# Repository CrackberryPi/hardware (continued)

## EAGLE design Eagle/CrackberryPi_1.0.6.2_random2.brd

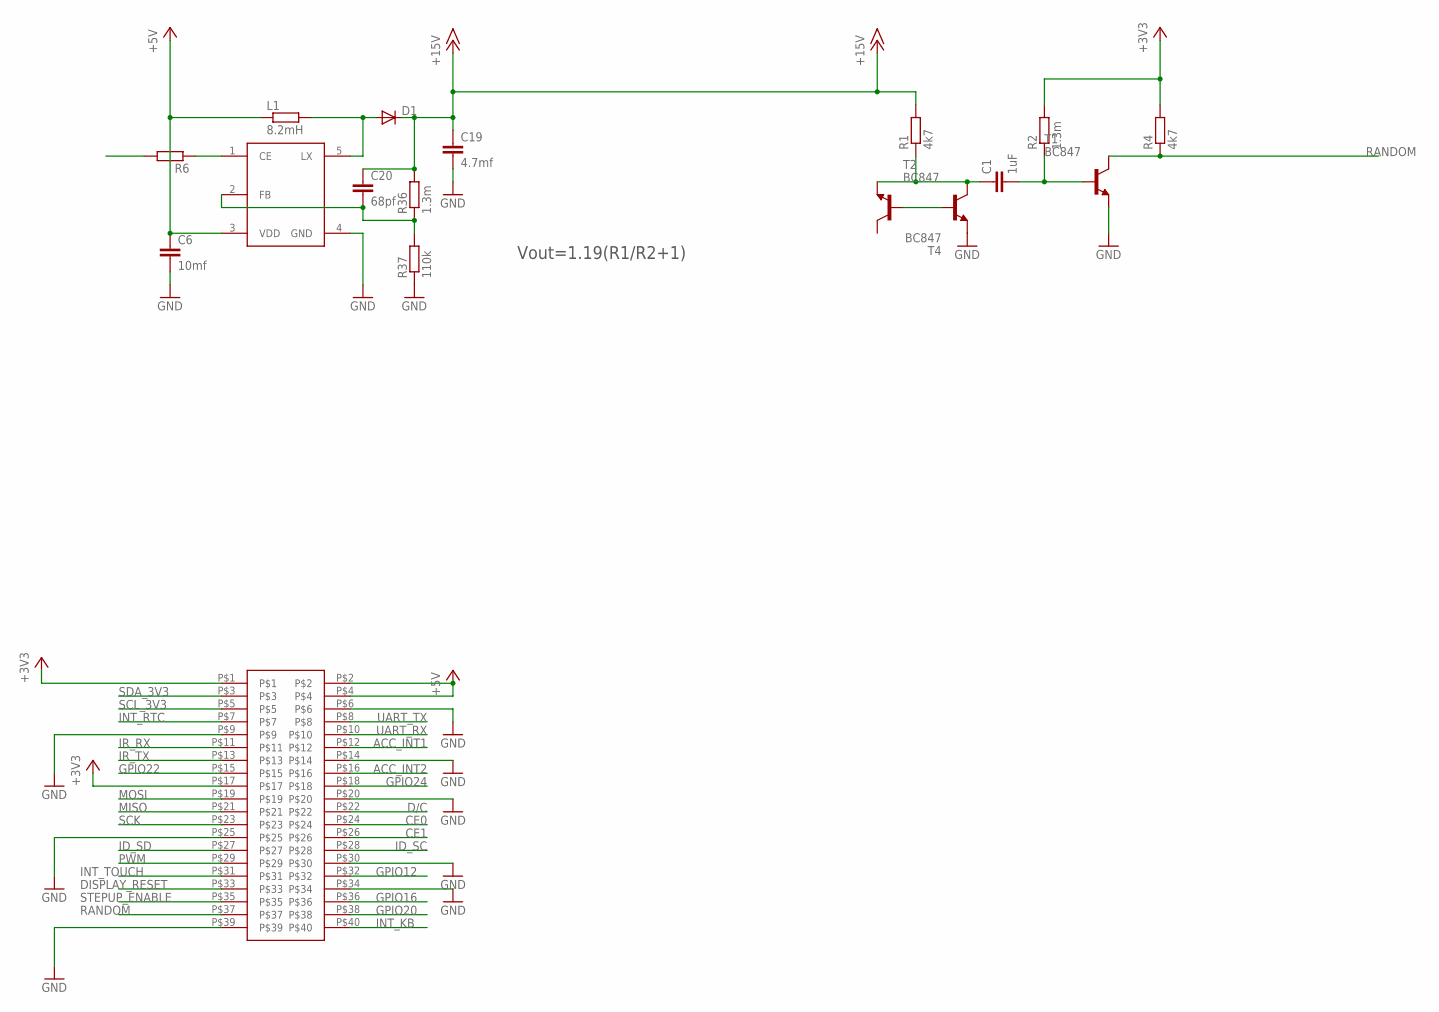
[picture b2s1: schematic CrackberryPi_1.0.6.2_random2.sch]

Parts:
C1: 1uF; C0603
C6: 10mf; C0603
C19: 4.7mf; C0603
C20: 68pf; C0603
D1: DIODE-SOD123; SOD123
L1: 8.2mH; R1210
R1, R4: 4k7; R0603
R2, R36: 1.3m; R0603
R6: R-EU_R1210; R1210
R37: 110k; R0603
T1, T2, T4: BC847; SOT23
U$2: NCP1406; SOT23-5L
U$11: HEADER; 20X2

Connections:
+3V3: R2.2, R4.2, U$11.P$1, U$11.P$17
+5V: C6.1, L1.1, U$2.3 (VDD), U$11.P$2, U$11.P$4
+15V: C19.1, C20.1, D1.C, R1.2, R36.2
ACC_INT1: U$11.P$12
ACC_INT2: U$11.P$16
CE0: U$11.P$24
CE1: U$11.P$26
D/C: U$11.P$22
DISPLAY_RESET: U$11.P$33
FB: C20.2, R36.1, R37.2, U$2.2 (FB)
GND: C6.2, C19.2, R37.1, T1.2 (E), T2.2 (E), U$2.4 (GND), U$11.P$6, U$11.P$9, U$11.P$14, U$11.P$20, U$11.P$25, U$11.P$30, U$11.P$34, U$11.P$39
GPIO12: U$11.P$32
GPIO16: U$11.P$36
GPIO20: U$11.P$38
GPIO22: U$11.P$15
GPIO24: U$11.P$18
ID_SC: U$11.P$28
ID_SD: U$11.P$27
INT_KB: U$11.P$40
INT_RTC: U$11.P$7
INT_TOUCH: U$11.P$31
IR_RX: U$11.P$11
IR_TX: U$11.P$13
LX: D1.A, L1.2, U$2.5 (LX)
MISO: U$11.P$21
MOSI: U$11.P$19
unnamed: R6.1, U$2.1 (CE)
unnamed: T2.1 (B), T4.1 (B)
unnamed: C1.1, R1.1, T2.3 (C), T4.2 (E)
unnamed: C1.2, R2.1, T1.1 (B)
PWM: U$11.P$29
RANDOM: R4.1, T1.3 (C), U$11.P$37
SCK: U$11.P$23
SCL_3V3: U$11.P$5
SDA_3V3: U$11.P$3
STEPUP_ENABLE: R6.2, U$11.P$35
UART_RX: U$11.P$10
UART_TX: U$11.P$8

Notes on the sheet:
Vout=1.19(R1/R2+1)

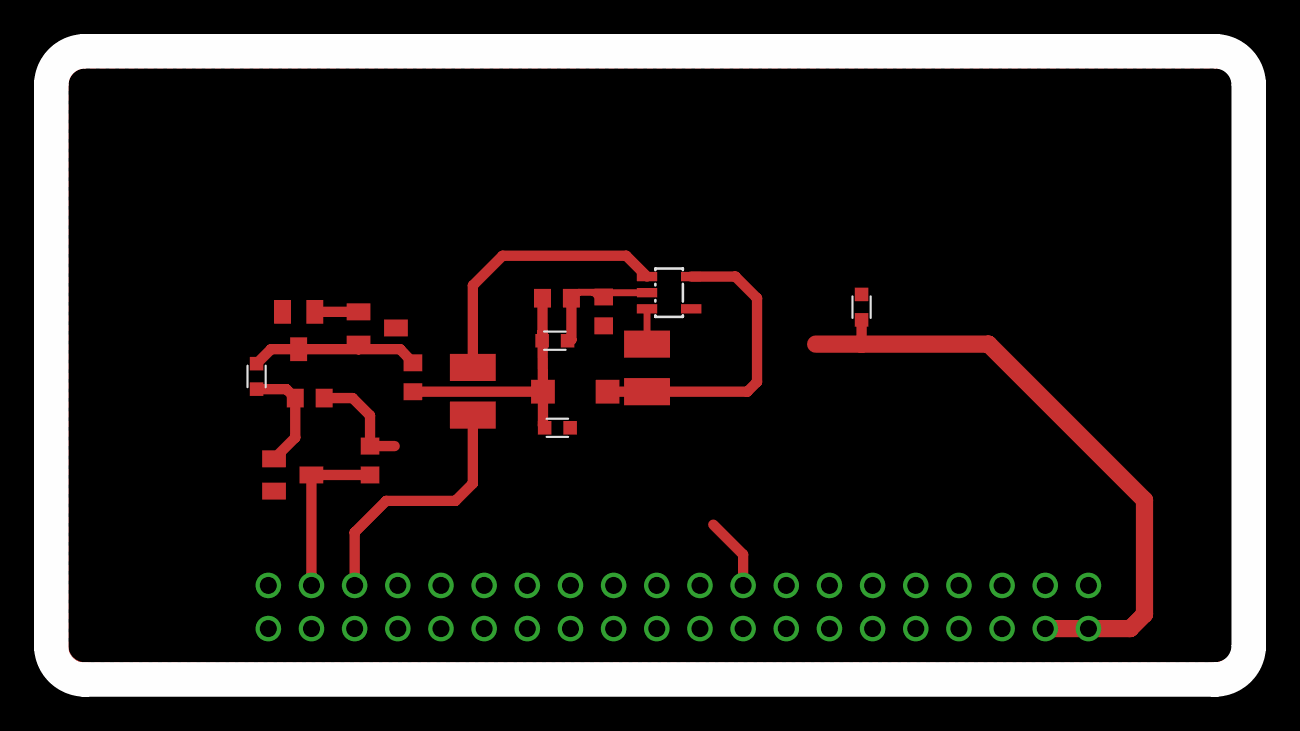
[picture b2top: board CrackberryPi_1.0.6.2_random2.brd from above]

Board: 2 copper layers, 70.5 x 37.0 mm, 17 parts (0 on the bottom side), 12 nets.

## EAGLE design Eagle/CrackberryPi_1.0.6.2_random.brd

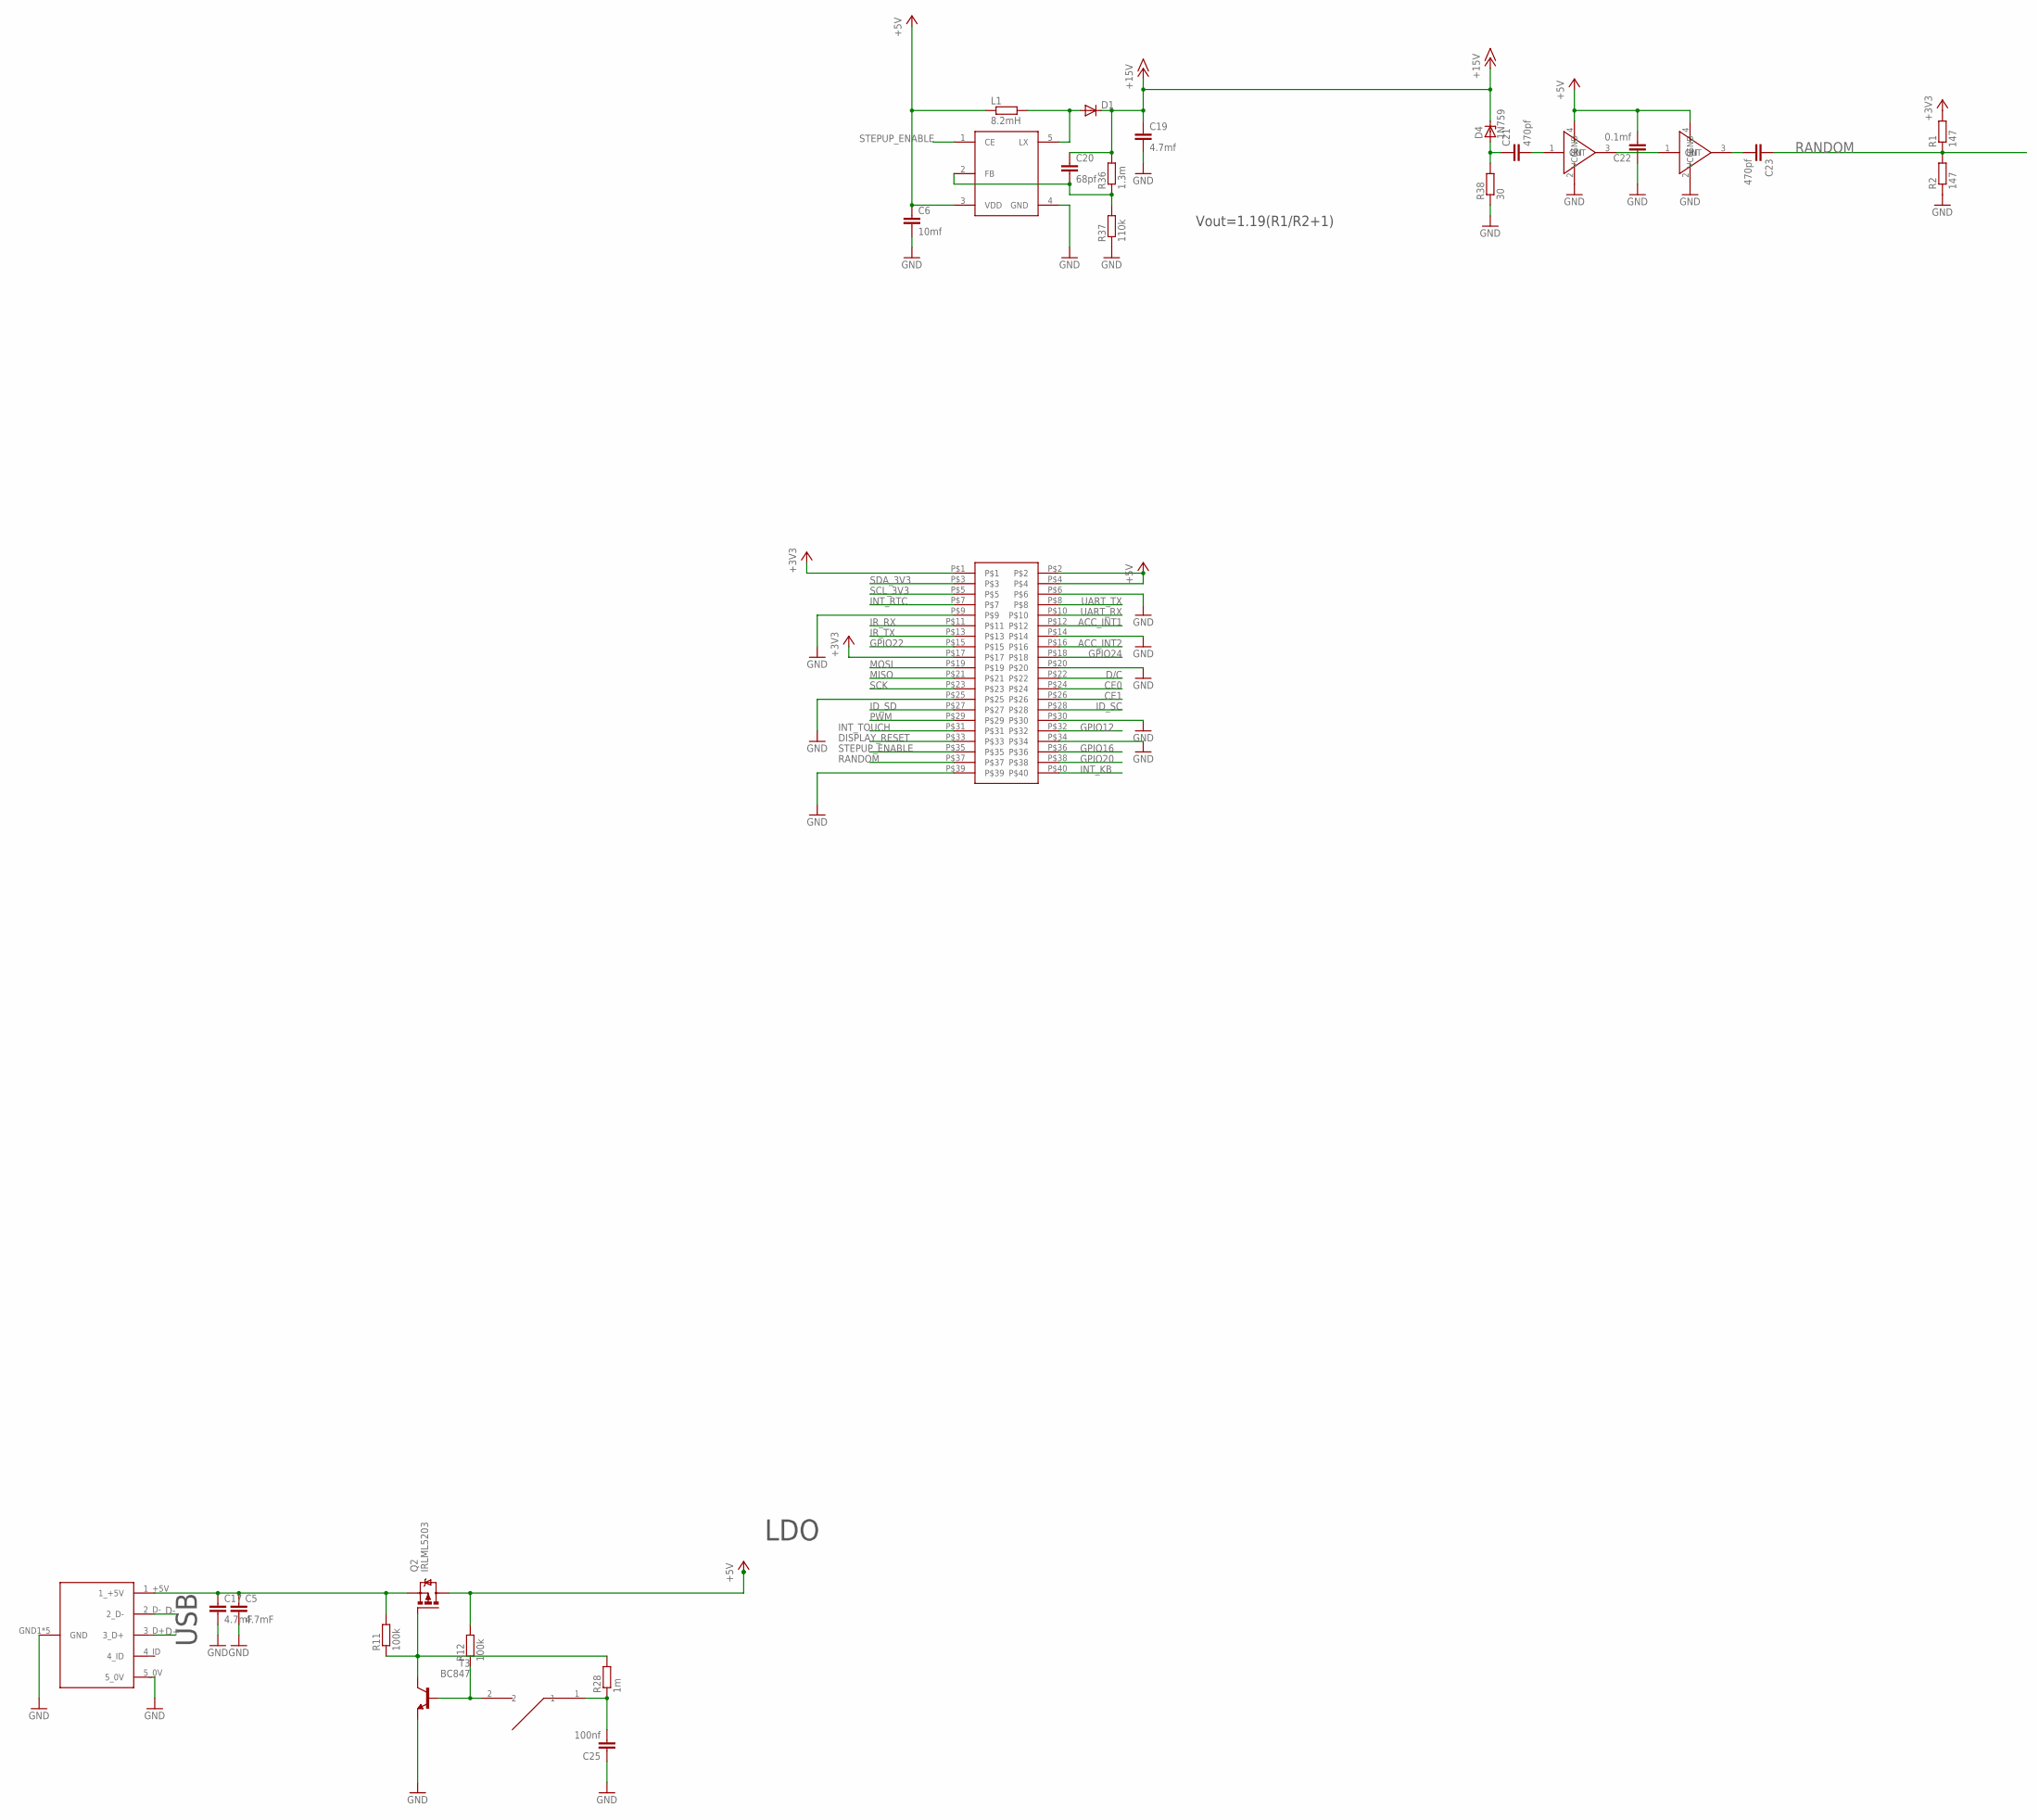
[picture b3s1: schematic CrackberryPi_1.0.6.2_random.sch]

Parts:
C5, C17: 4.7mF; C0603
C6: 10mf; C0603
C19: 4.7mf; C0603
C20: 68pf; C0603
C21, C23: 470pf; C0603
C22: 0.1mf; C0603
C25: 100nf; C0603
D1: DIODE-SOD123; SOD123
D4: 1N759; SOD80C
L1: 8.2mH; R1210
Q2: IRLML5203; MICRO3
R1, R2: 147; R0603
R11, R12: 100k; R0603
R28: 1m; R0603
R36: 1.3m; R0603
R37: 110k; R0603
R38: 30; R0603
T3: BC847; SOT23
U$2: NCP1406; SOT23-5L
U$3, U$10: MAX2650; SOT143-W
U$8: MOMSWITCH
U$9: MICRO_USB
U$11: HEADER; 20X2

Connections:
+3V3: R1.2, U$11.P$1, U$11.P$17
+5V: C6.1, C22.2, L1.1, Q2.3 (D), R12.2, U$2.3 (VDD), U$3.4 (VCC), U$10.4 (VCC), U$11.P$2, U$11.P$4
+15V: C19.1, C20.1, D1.C, D4.C, R36.2
ACC_INT1: U$11.P$12
ACC_INT2: U$11.P$16
CE0: U$11.P$24
CE1: U$11.P$26
D+: U$9.3_D+
D-: U$9.2_D-
D/C: U$11.P$22
DISPLAY_RESET: U$11.P$33
FB: C20.2, R36.1, R37.2, U$2.2 (FB)
GATE: Q2.1 (G), R11.1, R28.2, T3.3 (C)
GND: C5.2, C6.2, C17.2, C19.2, C22.1, C25.1, R2.1, R37.1, R38.1, T3.2 (E), U$2.4 (GND), U$3.2 (GND), U$9.5_0V, U$9.GND1 (GND), U$9.GND2 (GND), U$9.GND5 (GND), U$9.P$1 (GND), U$9.P$7 (GND), U$10.2 (GND), U$11.P$6, U$11.P$9, U$11.P$14, U$11.P$20, U$11.P$25, U$11.P$30, U$11.P$34, U$11.P$39
GPIO12: U$11.P$32
GPIO16: U$11.P$36
GPIO20: U$11.P$38
GPIO22: U$11.P$15
GPIO24: U$11.P$18
ID_SC: U$11.P$28
ID_SD: U$11.P$27
INT_KB: U$11.P$40
INT_RTC: U$11.P$7
INT_TOUCH: U$11.P$31
IN_1: C21.2, U$3.1 (IN)
IR_RX: U$11.P$11
IR_TX: U$11.P$13
LX: D1.A, L1.2, U$2.5 (LX)
MISO: U$11.P$21
MOSI: U$11.P$19
unnamed: C5.1, C17.1, Q2.2 (S), R11.2, U$9.1_+5V
unnamed: C21.1, D4.A, R38.2
unnamed: R12.1, T3.1 (B), U$8.2
unnamed: C25.2, R28.1, U$8.1
OUT1_IN2: U$3.3 (OUT), U$10.1 (IN)
OUT2: C23.2, U$10.3 (OUT)
PWM: U$11.P$29
RANDOM: C23.1, R1.1, R2.2, U$11.P$37
SCK: U$11.P$23
SCL_3V3: U$11.P$5
SDA_3V3: U$11.P$3
STEPUP_ENABLE: U$2.1 (CE), U$11.P$35
UART_RX: U$11.P$10
UART_TX: U$11.P$8

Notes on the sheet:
USB
LDO
Vout=1.19(R1/R2+1)

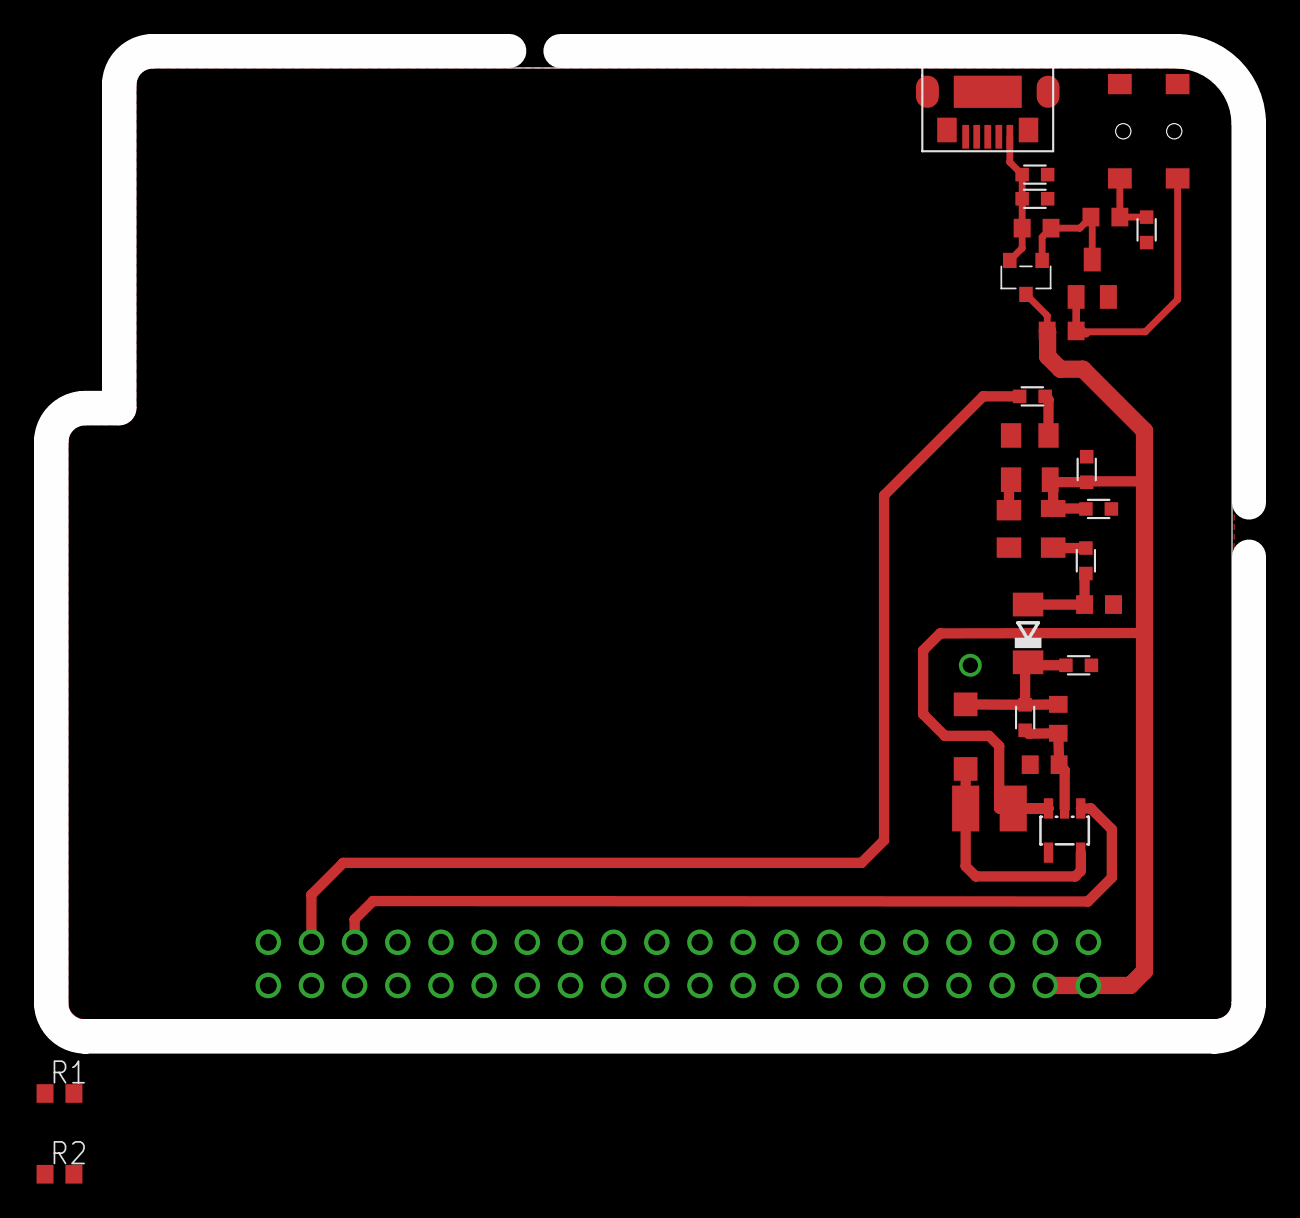
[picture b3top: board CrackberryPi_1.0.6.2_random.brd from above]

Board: 2 copper layers, 70.5 x 58.0 mm, 28 parts (0 on the bottom side), 16 nets.

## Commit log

2015-02-19 First setup and test
2015-02-19 Fixed to make image inline
2015-02-19 cropped image
2015-02-19 Further describing the plan, adding pictures
2015-02-19 Moved images to images/ subduer
2015-02-19 pics of hat and rtc
2015-02-19 eeprom data
2015-02-19 typo
2015-02-19 info on power circuit
2015-02-19 more info on power
2015-02-19 Added basic-sketch in SketchUp format
2015-02-19 PCB files
2015-02-19 Battery changes
2015-02-19 Added **/*~ to .gitignore and removed README.md~
2015-02-19 rpi2_stl
2015-02-19 Updated sketchup for battery size
2015-02-20 HAT EEPROM improvements
2015-02-20 Update on eeprom in readme
2015-02-20 screen
2015-02-20 scherm en touchscreen bestanden en info
2015-02-20 charging circuit
2015-02-20 typoos
2015-02-21 screen info
2015-02-21 screen circuitry picture
2015-02-21 eeprom pin-out check
2015-02-21 part selection
2015-02-25 pcb development
2015-03-08 finalizing pcb first proto
    schematics, library parts and gerber rar
2015-03-11 Revert "CAD designing casing"
    This reverts commit d44902fa8a798b026d4c9fe41ac44cd0e8bc14a0.
    Conflicts:
    CAD/Assembly.SLDASM
    CAD/Backup of Assembly.SLDASM
    CAD/Backup of Casing.SLDPRT
    CAD/BlackBox.PDF
2015-03-19 Added schematic png
2015-03-22 work on casing and pcb1.0.2
2015-03-22 documentatie pcb
2015-03-30 pictures, pcb advancements
2015-03-30 cleaning up
2015-03-30 cleaning
2015-03-30 uploading
2015-03-30 getting pics right
2015-03-30 charger change
2015-03-30 updating documentation
2015-03-30 pics
2015-03-30 rtc documentation
2015-03-30 gpio
2015-03-30 gpio_out
2015-03-30 fm transmitter
2015-03-30 keyboard controller
2015-03-30 BOM en IR
2015-04-05 screen documentation
2015-04-28 lots of pcb progress and iterations
2015-05-06 testing progress
2015-05-19 lots of updates
